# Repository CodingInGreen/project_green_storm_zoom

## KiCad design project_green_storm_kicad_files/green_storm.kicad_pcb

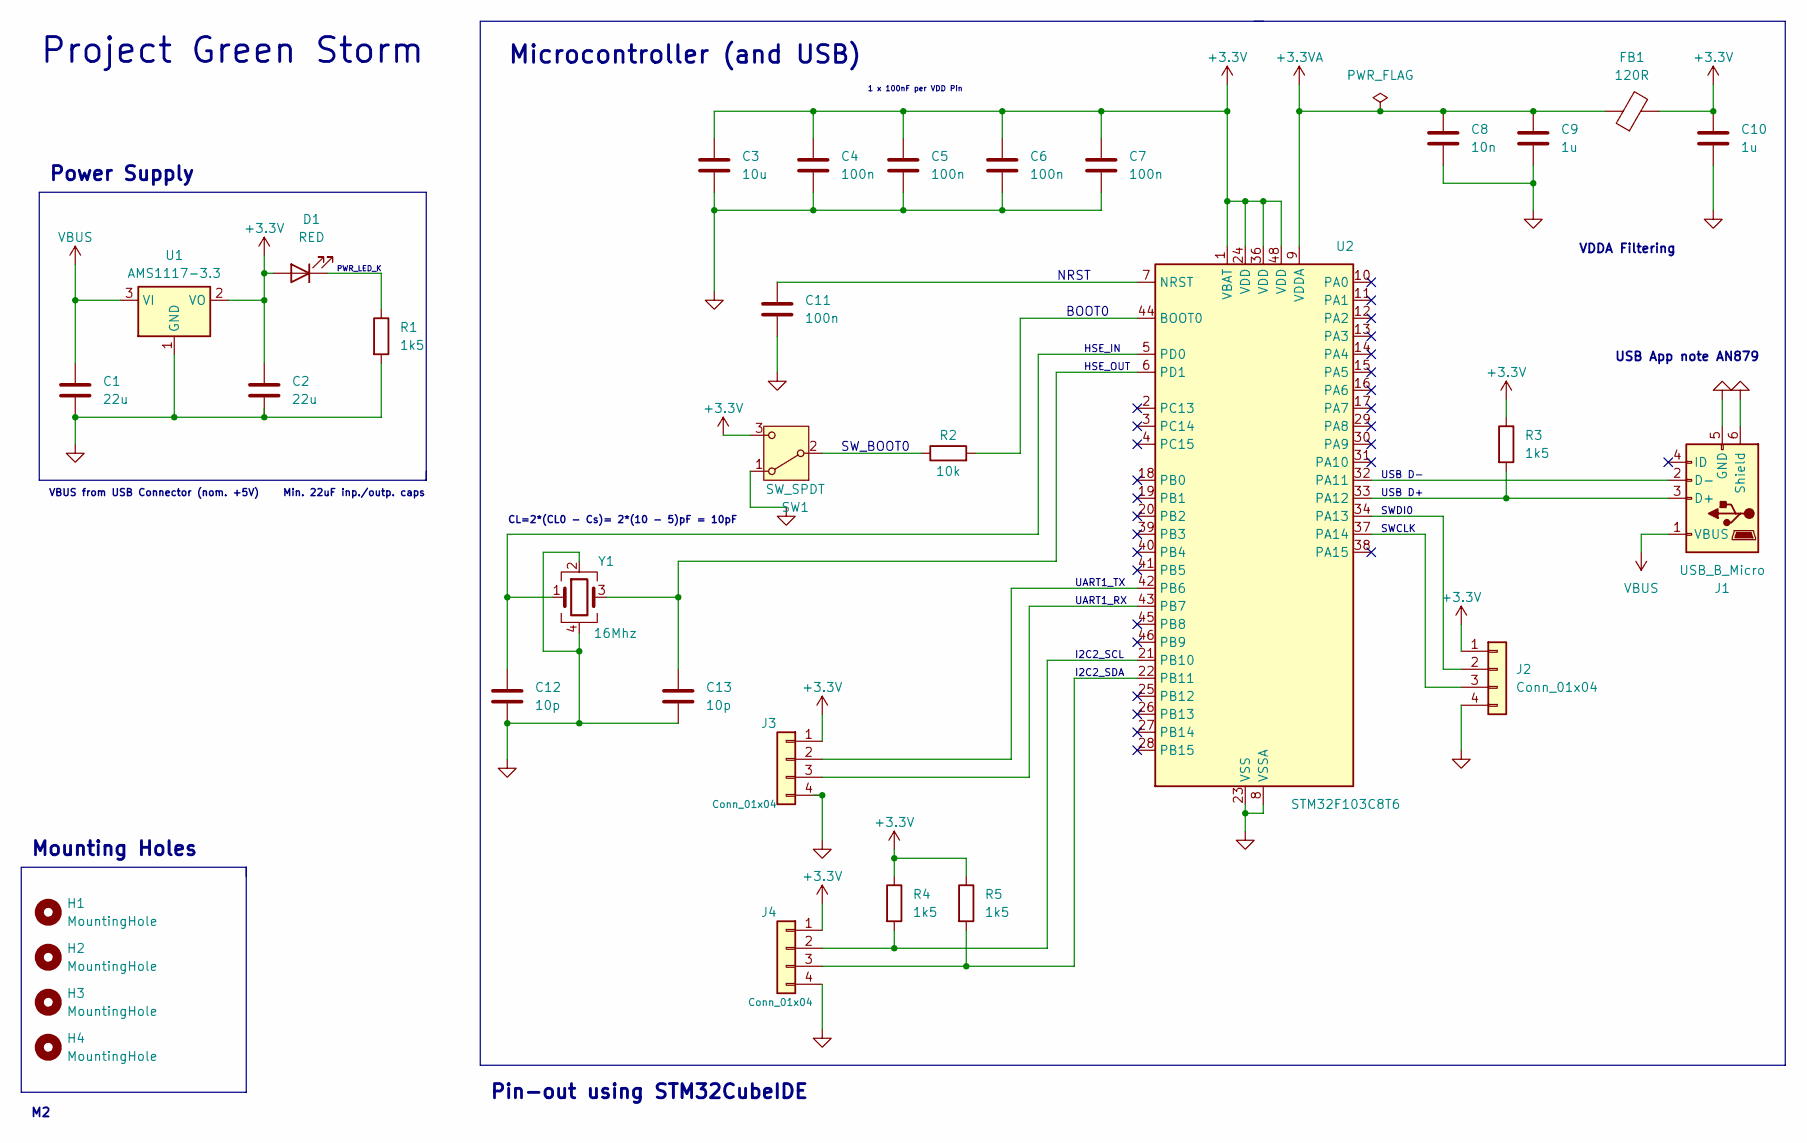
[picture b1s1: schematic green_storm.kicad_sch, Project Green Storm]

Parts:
C1, C2: 22u; C_0805_2012Metric
C3: 10u; C_0603_1608Metric
C4, C5, C6, C7, C11: 100n; C_0402_1005Metric
C8: 10n; C_0402_1005Metric
C9, C10: 1u; C_0402_1005Metric
C12, C13: 10p; C_0402_1005Metric
D1: RED; LED_0603_1608Metric
FB1: 120R; L_0603_1608Metric
H1, H2, H3, H4: MountingHole; MountingHole_2.2mm_M2
J1: USB_B_Micro; USB_Micro-B_Wuerth_629105150521
J2, J3, J4: Conn_01x04; PinHeader_1x04_P2.54mm_Vertical
R1, R3, R4, R5: 1k5; R_0402_1005Metric
R2: 10k; R_0402_1005Metric
SW1: SW_SPDT; SW_SPDT_PCM12
U1: AMS1117-3.3; SOT-223-3_TabPin2
U2: STM32F103C8T6; LQFP-48_7x7mm_P0.5mm
Y1: 16Mhz; Crystal_SMD_3225-4Pin_3.2x2.5mm

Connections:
+3.3V: C2.1, C3.1, C4.1, C5.1, C6.1, C7.1, C10.1, D1.2 (A), FB1.2, J2.1, J3.1, J4.1, R3.1, R4.1, R5.1, SW1.3 (C), U1.2 (VO), U2.1 (VBAT), U2.24 (VDD), U2.36 (VDD), U2.48 (VDD)
+3.3VA: C8.1, C9.1, FB1.1, U2.9 (VDDA)
GND: C1.2, C2.2, C3.2, C4.2, C5.2, C6.2, C7.2, C8.2, C9.2, C10.2, C11.2, C12.2, C13.2, J1.5 (GND), J1.6 (Shield), J2.4, J3.4, J4.4, R1.2, SW1.1 (A), U1.1 (GND), U2.8 (VSSA), U2.23 (VSS), U2.35 (VSS), U2.47 (VSS), Y1.2, Y1.4
unnamed: D1.1 (K), R1.1
unnamed: J1.3 (D+), R3.2, U2.33 (PA12)
unnamed: J1.2 (D-), U2.32 (PA11)
unnamed: J2.2, U2.34 (PA13)
unnamed: J2.3, U2.37 (PA14)
unnamed: J3.2, U2.42 (PB6)
unnamed: J3.3, U2.43 (PB7)
unnamed: J4.2, R4.2, U2.21 (PB10)
unnamed: J4.3, R5.2, U2.22 (PB11)
unnamed: R2.1, SW1.2 (B)
unnamed: R2.2, U2.44 (BOOT0)
unnamed: C11.1, U2.7 (NRST)
unnamed: C12.1, U2.5 (PD0), Y1.1
unnamed: C13.1, U2.6 (PD1), Y1.3
VBUS: C1.1, J1.1 (VBUS), U1.3 (VI)

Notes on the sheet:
HSE_IN
USB D-
I2C2_SDA
I2C2_SCL
Min. 22uF inp./outp. caps
VDDA Filtering
CL=2*(CL0 - Cs)= 2*(10 - 5)pF = 10pF
NRST
Power Supply
BOOT0
Microcontroller (and USB)
USB App note AN879
Mounting Holes
SWDI0
Pin-out using STM32CubeIDE
Project Green Storm
VBUS from USB Connector (nom. +5V)
1 x 100nF per VDD Pin
UART1_RX
PWR_LED_K
UART1_TX
SWCLK
HSE_OUT
USB D+
SW_BOOT0

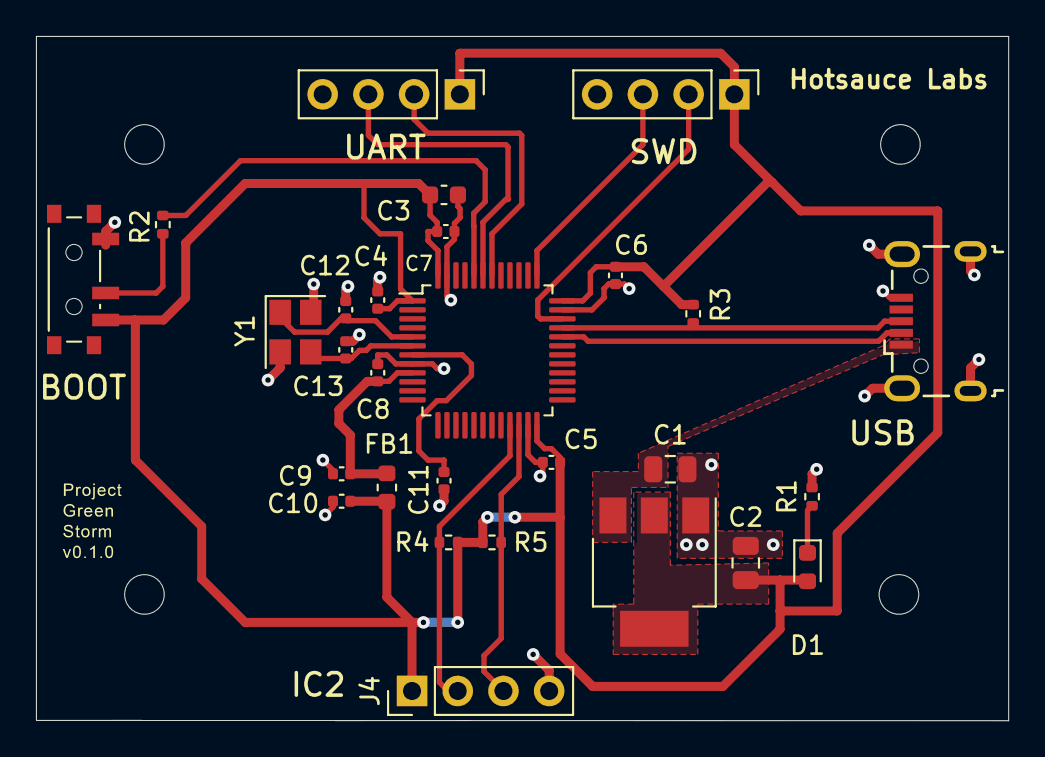
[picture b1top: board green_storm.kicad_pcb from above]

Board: 2 copper layers, 54.0 x 38.0 mm, 32 parts (0 on the bottom side), 18 nets.

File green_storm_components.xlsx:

Ref | Qnty | Value | Footprint | Cmp name | Description | Vendor | DNP
C1, C2 | 2 | 22u | Capacitor_SMD:C_0805_2012Metric | C | Unpolarized capacitor | Mouser | 80-C0805C226K9PACTU
C3 | 1 | 10u | Capacitor_SMD:C_0603_1608Metric | C | Unpolarized capacitor
C4, C5, C6, C7, C11 | 5 | 100n | Capacitor_SMD:C_0402_1005Metric | C | Unpolarized capacitor | Mouser | 80-C0402C104M8R
C8 | 1 | 10n | Capacitor_SMD:C_0402_1005Metric | C | Unpolarized capacitor
C9, C10 | 2 | 1u | Capacitor_SMD:C_0402_1005Metric | C | Unpolarized capacitor
C12, C13 | 2 | 10p | Capacitor_SMD:C_0402_1005Metric | C | Unpolarized capacitor | Mouser | 581-04026D100JAT2A
D1 | 1 | RED | LED_SMD:LED_0603_1608Metric | LED | Light emitting diode
FB1 | 1 | 120R | Inductor_SMD:L_0603_1608Metric | FerriteBead | Ferrite bead | Digi-Key | 240-2367-2-ND
J1 | 1 | USB_B_Micro | Connector_USB:USB_Micro-B_Wuerth_629105150521 | USB_B_Micro | USB Micro Type B connector | Mouser | 710-629105150521
J2, J3, J4 | 3 | Conn_01x04 | Connector_PinHeader_2.54mm:PinHeader_1x04_P2.54mm_Vertical | Conn_01x04 | Generic connector, single row, 01x04, script generated (kicad-library-utils/sch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 | Mouser | 200-TSW10424TS
R1, R3, R4, R5 | 4 | 1k5 | Resistor_SMD:R_0402_1005Metric | R_2 | Resistor
R2 | 1 | 10k | Resistor_SMD:R_0402_1005Metric | R | Resistor | Digi-Key | P17230CT-ND
SW1 | 1 | SW_SPDT | Button_Switch_SMD:SW_SPDT_PCM12 | SW_SPDT | Switch, single pole double throw | Mouser | 611-PCM12SMTBR
U1 | 1 | AMS1117-3.3 | Rua Dr. Joaquim Eleutério Gaspar Gomes, 24A, 1° | AMS1117-3.3 | 1A Low Dropout regulator, positive, 3.3V fixed output, SOT-223
U2 | 1 | STM32F103C8T6 | Queluz, Portugal 2745-133 | STM32F103C8Tx | STMicroelectronics Arm Cortex-M3 MCU, 64KB flash, 20KB RAM, 72 MHz, 2.0-3.6V, 3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
Y1 | 1 | 16Mhz | Crystal:Crystal_SMD_3225-4Pin_3.2x2.5mm | Crystal_GND24 | Four pin crystal, GND on pins 2 and 4 | Mouser | 581-CX3225GB16PHPQCC
 | 28
 | Soldered by Hand
 | Assembled by JLCPCB

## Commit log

2024-01-31 Photo commit
2024-01-31 Add schematics and pcb layout
2024-04-01 Add kicad files
2024-04-09 Update spreadsheet with links
